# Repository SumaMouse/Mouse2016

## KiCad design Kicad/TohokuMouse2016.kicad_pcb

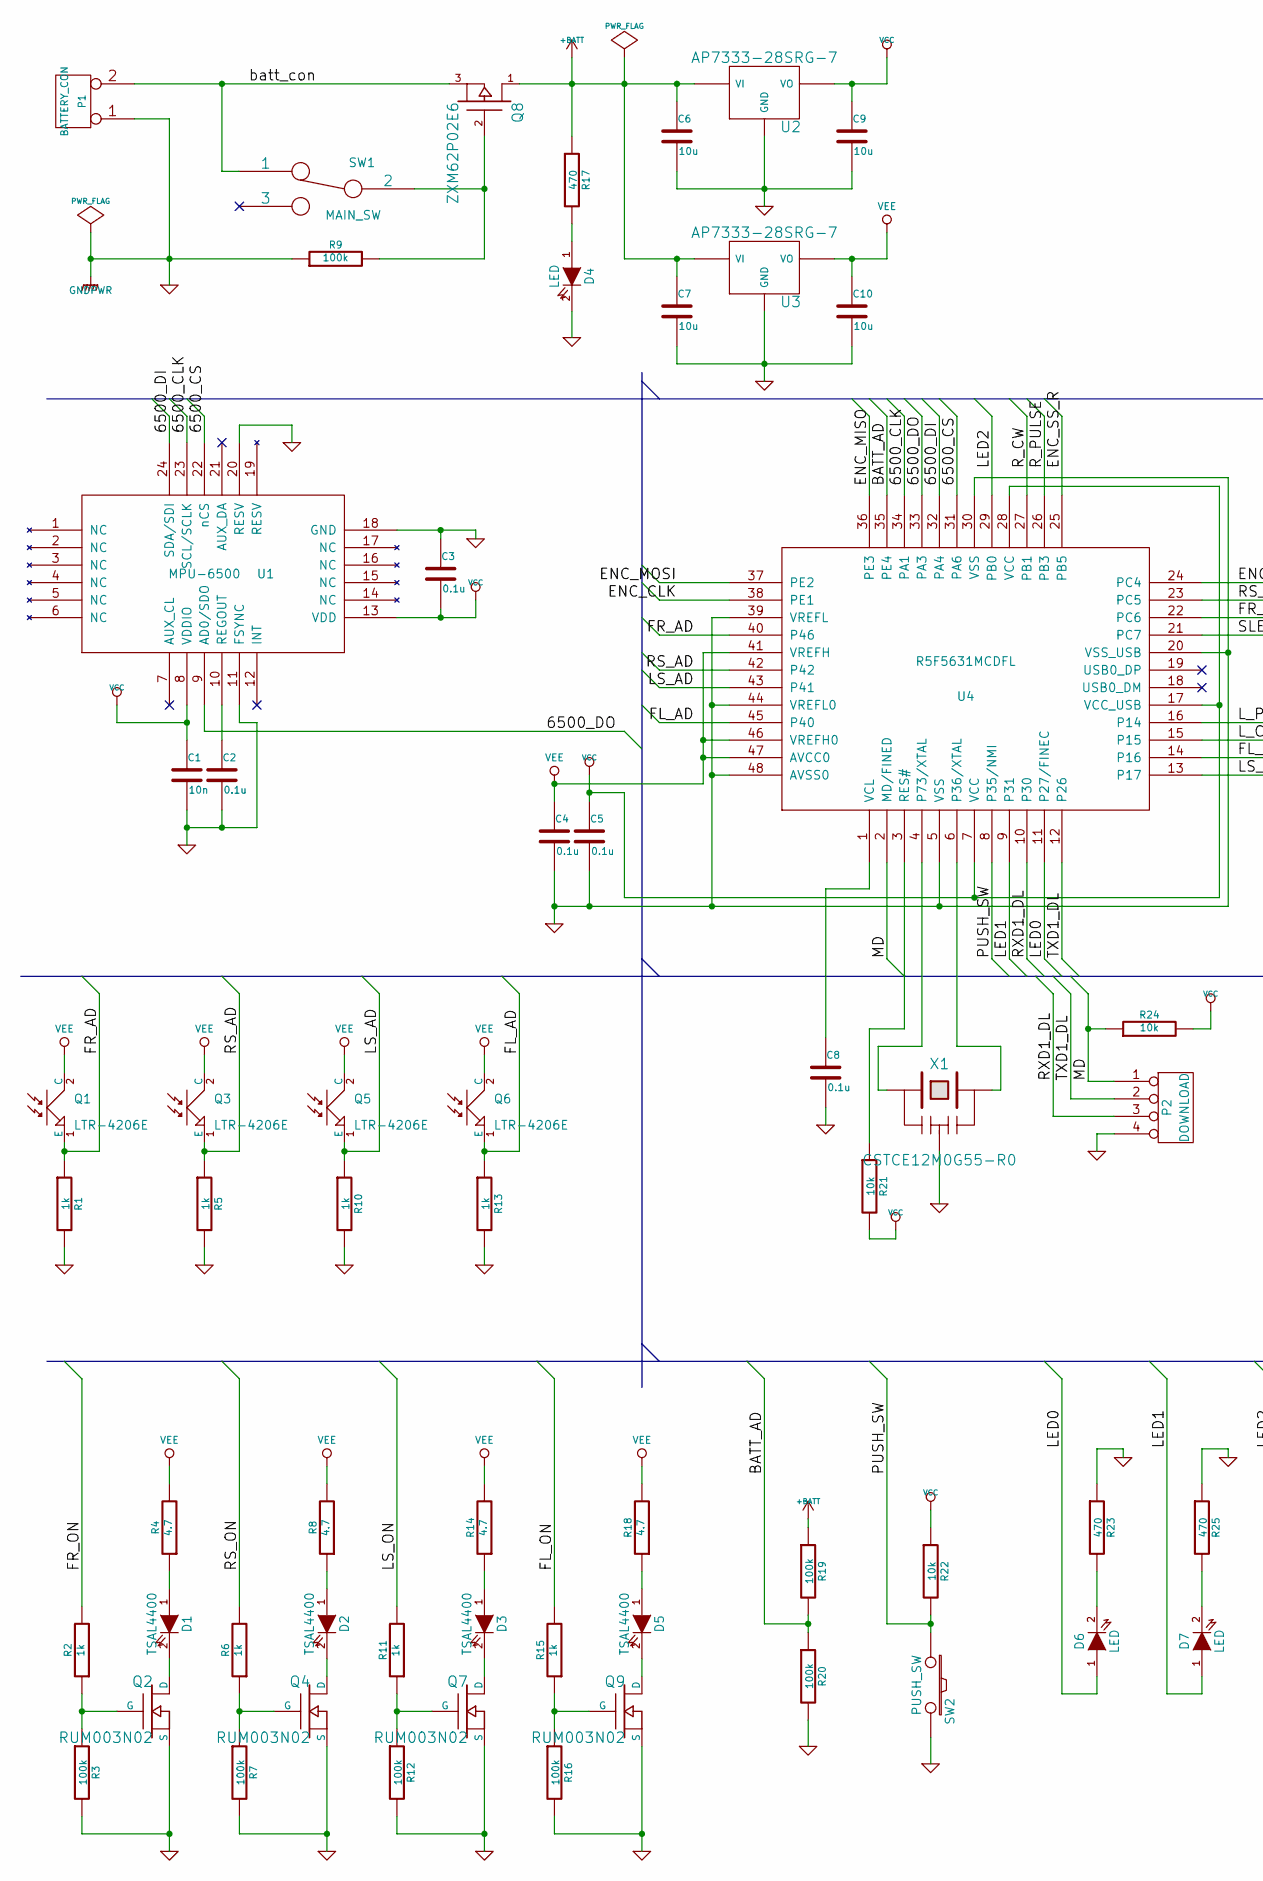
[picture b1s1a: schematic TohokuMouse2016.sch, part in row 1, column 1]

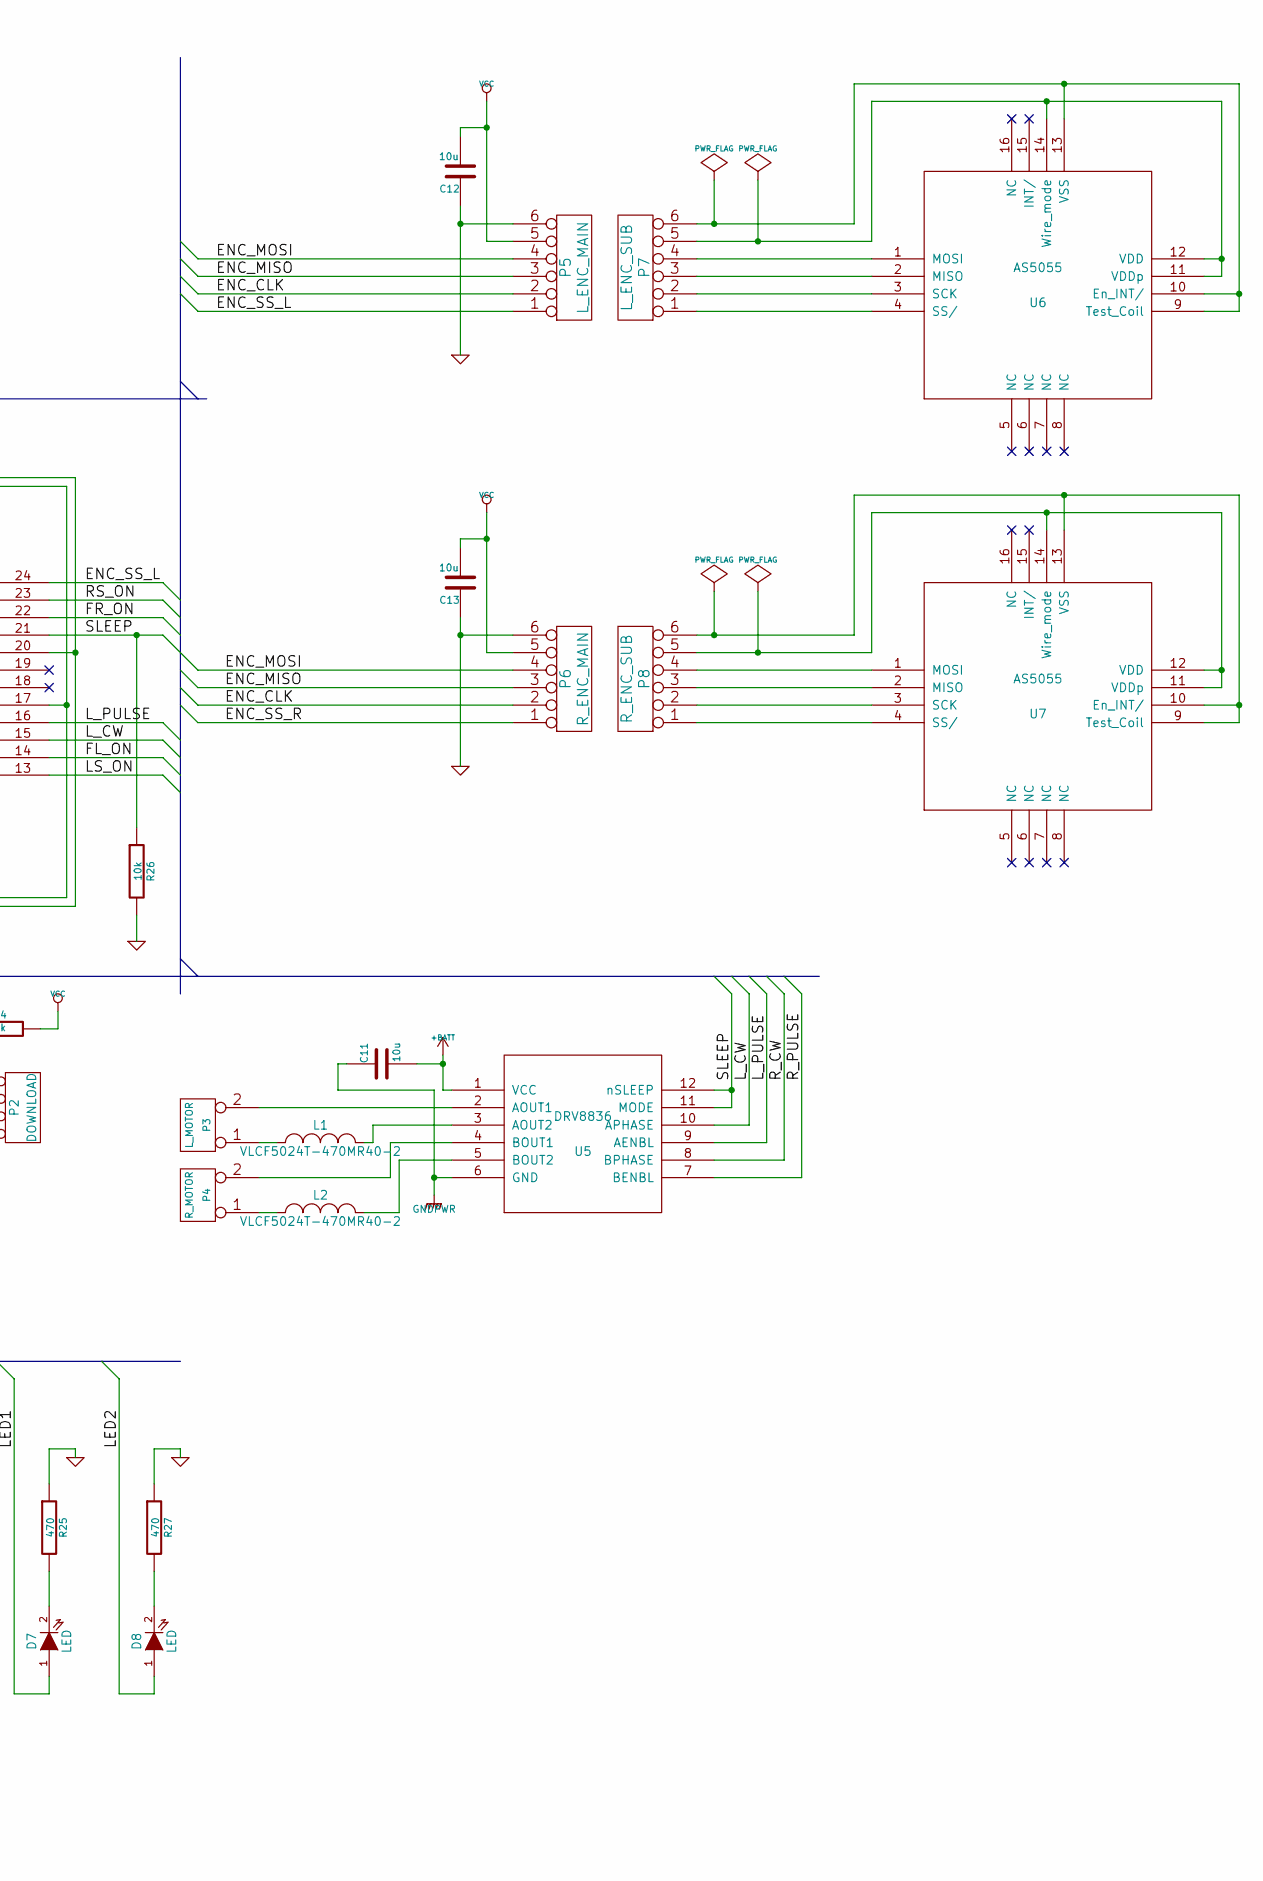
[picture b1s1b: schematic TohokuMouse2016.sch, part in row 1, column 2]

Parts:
C1: 10n; Chip_2012
C2, C3, C4, C5, C8: 0.1u; Chip_1005
C6, C7, C9, C10, C11, C12, C13: 10u; Chip_2012
D1, D2, D3, D5: TSAL4400
D4, D6, D7, D8: LED; Chip_2012
L1, L2: VLCF5024T-470MR40-2; VLCF4018_2
P1: BATTERY_CON; BATT_CON
P2: DOWNLOAD; Download
P3: L_MOTOR; MotorConnect
P4: R_MOTOR; MotorConnect
P5: L_ENC_MAIN; EncConn
P6: R_ENC_MAIN; EncConn
P7: L_ENC_SUB; EncConn
P8: R_ENC_SUB; EncConn
Q1, Q3, Q5, Q6: LTR-4206E; LTR_4206E
Q2, Q4, Q7, Q9: RUM003N02
Q8: ZXM62P02E6
R1, R2, R5, R6, R10, R11, R13, R15: 1k; Chip_1005
R3, R7, R9, R12, R16, R19, R20: 100k; Chip_1005
R4, R8, R14, R18: 4.7; Chip_1005
R17, R23, R25, R27: 470; Chip_1005
R21, R22, R24, R26: 10k; Chip_1005
SW1: MAIN_SW; SW_SPDT_PCM12
SW2: PUSH_SW; SW_SPST_EVQPE1
U1: MPU-6500; MPU6500
U2, U3: AP7333-28SRG-7; AP7333_xxSR
U4: R5F5631MCDFL
U5: DRV8836
U6, U7: AS5055
X1: CSTCE12M0G55-R0; CSTE12M0G55_R0

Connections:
+BATT: C6.1, C7.1, C11.2, Q8.1 (D), R17.1, R19.1, U2.VI, U3.VI, U5.1 (VCC)
/6500_CLK: U1.23 (SCL/SCLK), U4.34 (PA1)
/6500_CS: U1.22 (nCS), U4.31 (PA6)
/6500_DI: U1.24 (SDA/SDI), U4.32 (PA4)
/6500_DO: U1.9 (AD0/SDO), U4.33 (PA3)
/BATT_AD: R19.2, R20.1, U4.35 (PE4)
/ENC_CLK: P5.2, P6.2, U4.38 (PE1)
/ENC_MISO: P5.3, P6.3, U4.36 (PE3)
/ENC_MOSI: P5.4, P6.4, U4.37 (PE2)
/ENC_SS_L: P5.1, U4.24 (PC4)
/ENC_SS_R: P6.1, U4.25 (PB5)
/FL_AD: Q6.1 (E), R13.1, U4.45 (P40)
/FL_ON: R15.2, U4.14 (P16)
/FR_AD: Q1.1 (E), R1.1, U4.40 (P46)
/FR_ON: R2.2, U4.22 (PC6)
/LED0: D6.1 (A), U4.11 (P27/FINEC)
/LED1: D7.1 (A), U4.9 (P31)
/LED2: D8.1 (A), U4.29 (PB0)
/LS_AD: Q5.1 (E), R10.1, U4.43 (P41)
/LS_ON: R11.2, U4.13 (P17)
/L_CW: U4.15, U5.10 (APHASE)
/L_PULSE: U4.16 (P14), U5.9 (AENBL)
/MD: P2.1, R24.1, U4.2 (MD/FINED)
/PUSH_SW: R22.2, SW2.1, U4.8 (P35/NMI)
/RS_AD: Q3.1 (E), R5.1, U4.42
/RS_ON: R6.2, U4.23 (PC5)
/RXD1_DL: P2.3, U4.10 (P30)
/R_CW: U4.27 (PB1), U5.8 (BPHASE)
/R_PULSE: U4.26 (PB3), U5.7 (BENBL)
/SLEEP: R26.1, U4.21 (PC7), U5.11 (MODE), U5.12 (nSLEEP)
/TXD1_DL: P2.2, U4.12 (P26)
/batt_con: P1.2, Q8.3 (S), SW1.1
GND: C1.2, C2.2, C3.1, C4.2, C5.2, C6.2, C7.2, C8.2, C9.2, C10.2, C11.1, C12.1, C13.1, D4.2 (K), P1.1, P2.4, P5.6, P6.6, Q2.S, Q4.S, Q7.S, Q9.S, R1.2, R3.2, R5.2, R7.2, R9.1, R10.2, R12.2, R13.2, R16.2, R20.2, R23.1, R25.1, R26.2, R27.1, SW2.2, U1.11 (FSYNC), U1.18 (GND), U1.20 (RESV), U2.GND, U3.GND, U4.5 (VSS), U4.20 (VSS_USB), U4.30 (VSS), U4.39 (VREFL), U4.44 (VREFL0), U4.48 (AVSS0), U5.6 (GND), X1.3
unnamed: C2.1, U1.10 (REGOUT)
unnamed: C8.1, U4.1 (VCL)
unnamed: D1.1 (A), R4.1
unnamed: D1.2 (K), Q2.D
unnamed: D2.1 (A), R8.1
unnamed: D2.2 (K), Q4.D
unnamed: D3.1 (A), R14.1
unnamed: D3.2 (K), Q7.D
unnamed: D4.1 (A), R17.2
unnamed: D5.1 (A), R18.1
unnamed: D5.2 (K), Q9.D
unnamed: D6.2 (K), R23.2
unnamed: D7.2 (K), R25.2
unnamed: D8.2 (K), R27.2
unnamed: L1.1, P3.1
unnamed: L1.2, U5.3 (AOUT2)
unnamed: L2.1, P4.1
unnamed: L2.2, U5.5 (BOUT2)
unnamed: P3.2, U5.2 (AOUT1)
unnamed: P4.2, U5.4 (BOUT1)
unnamed: P7.1, U6.4 (SS/)
unnamed: P7.2, U6.3 (SCK)
unnamed: P7.3, U6.2 (MISO)
unnamed: P7.4, U6.1 (MOSI)
unnamed: P7.5, U6.11 (VDDp), U6.12 (VDD), U6.14 (Wire_mode)
unnamed: P7.6, U6.9 (Test_Coil), U6.10 (En_INT/), U6.13 (VSS)
unnamed: P8.1, U7.4 (SS/)
unnamed: P8.2, U7.3 (SCK)
unnamed: P8.3, U7.2 (MISO)
unnamed: P8.4, U7.1 (MOSI)
unnamed: P8.5, U7.11 (VDDp), U7.12 (VDD), U7.14 (Wire_mode)
unnamed: P8.6, U7.9 (Test_Coil), U7.10 (En_INT/), U7.13 (VSS)
unnamed: Q2.G, R2.1, R3.1
unnamed: Q4.G, R6.1, R7.1
unnamed: Q7.G, R11.1, R12.1
unnamed: Q8.2 (G), R9.2, SW1.2
unnamed: Q9.G, R15.1, R16.1
unnamed: R21.1, U4.3 (RES#)
unnamed: U4.4 (P73/XTAL), X1.1
unnamed: U4.6 (P36/XTAL), X1.2
VCC: C1.1, C3.2, C5.1, C9.1, C12.2, C13.2, P5.5, P6.5, R21.2, R22.1, R24.2, U1.8 (VDDIO), U1.13 (VDD), U2.VO, U4.7 (VCC), U4.17 (VCC_USB), U4.28 (VCC)
VEE: C4.1, C10.1, Q1.2 (C), Q3.2 (C), Q5.2 (C), Q6.2 (C), R4.2, R8.2, R14.2, R18.2, U3.VO, U4.41 (VREFH), U4.46 (VREFH0), U4.47 (AVCC0)

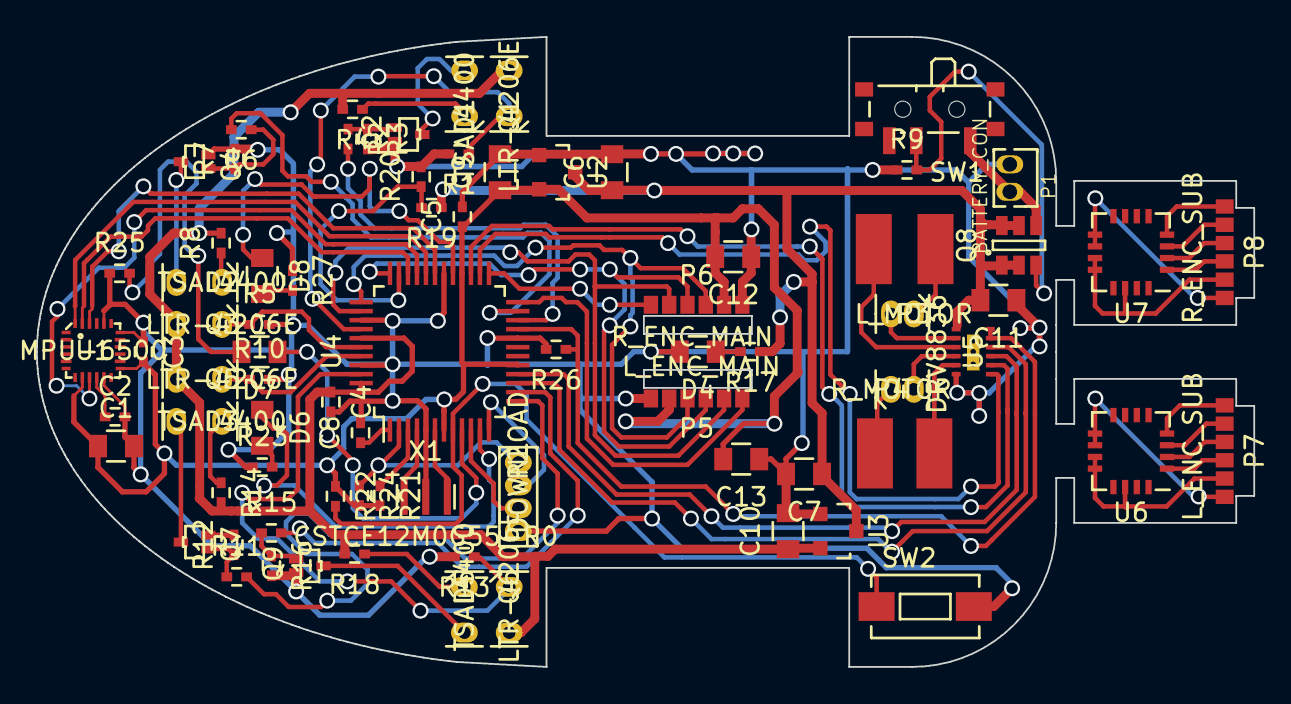
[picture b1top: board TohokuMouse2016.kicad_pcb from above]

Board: 2 copper layers, 67.6 x 35.0 mm, 77 parts (0 on the bottom side), 75 nets.

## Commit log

2016-01-09 test
2016-01-10 Added clock setting.
2016-01-25 Added device test
2016-01-25 Added parts list.
2016-01-25 Added datasheets
2016-01-25 Update parts list
2016-02-03 ADC Test
2016-02-09 Simple SPI by SCI.
2016-02-09 Update SPI
2016-07-03 Ready to PCB edit.
2016-07-09 Added mech data.
2016-07-09 update mech data.
2016-07-14 Update circuitdiagram.
2016-07-16 Order to elerow.
2016-09-25 MototTestOK
2017-07-01 Toki got the "Enkaigei".
    Toki got the "Enkaigei".
